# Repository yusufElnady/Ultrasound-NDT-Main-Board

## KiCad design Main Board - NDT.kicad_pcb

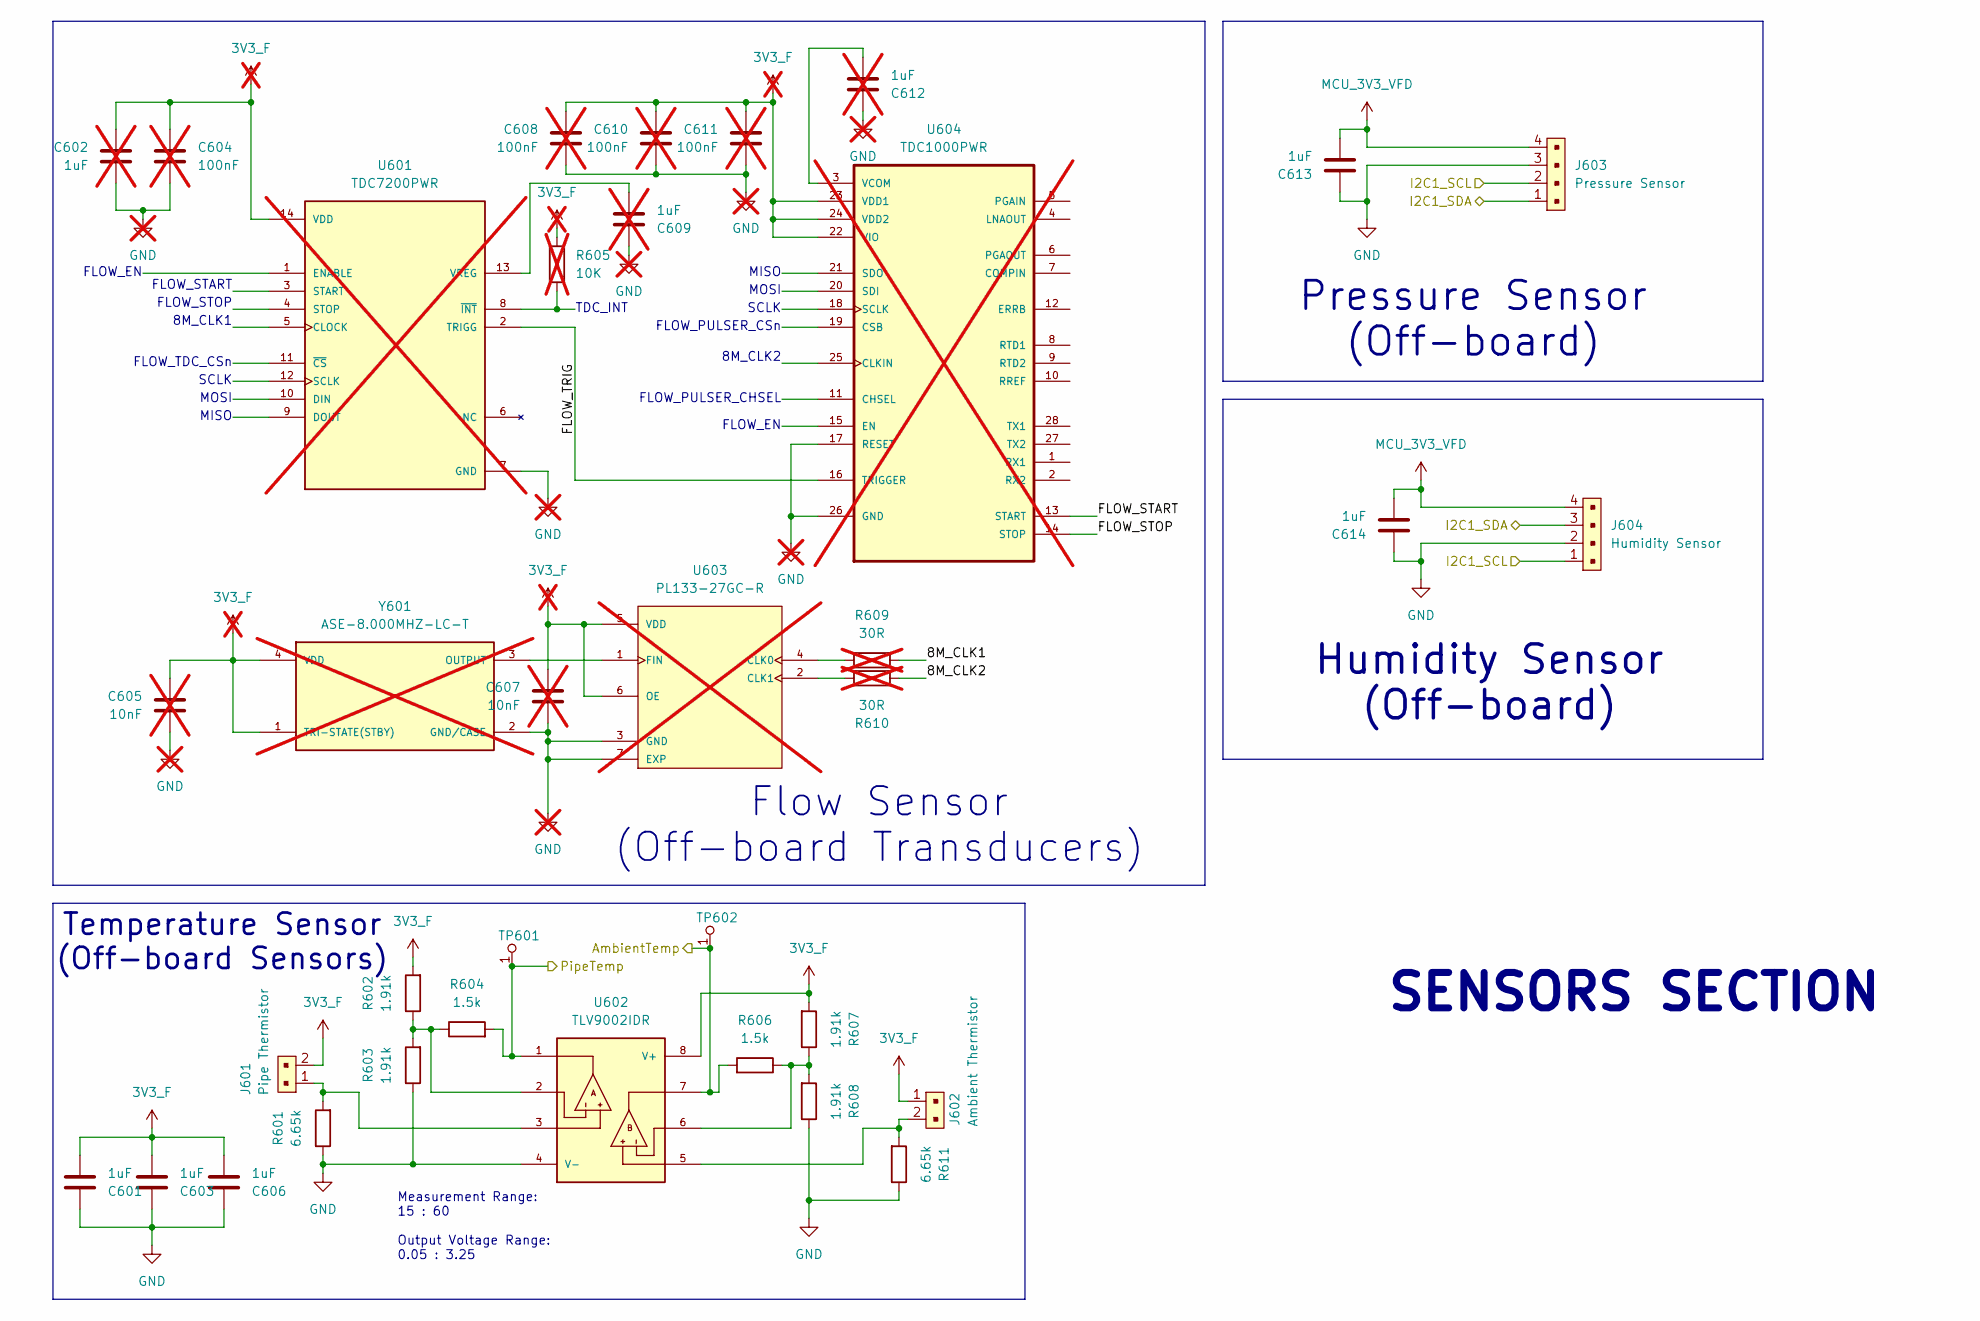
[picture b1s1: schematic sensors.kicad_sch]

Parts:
C601, C603, C606, C613, C614: 1uF; C_0603_1608Metric
C602, C609, C612: 1uF; not fitted
C604, C608, C610, C611: 100nF; C_0603_1608Metric; not fitted
C605, C607: 10nF; C_0603_1608Metric; not fitted
J601: Pipe Thermistor; PinHeader_1x2_P2mm_Drill1mm_RA; MPN S2B-PH-K-S(LF)(SN); Digi-Key_PN 455-1719-ND
J602: Ambient Thermistor; PinHeader_1x2_P2mm_Drill1mm_RA; MPN S2B-PH-K-S(LF)(SN); Digi-Key_PN 455-1719-ND
J603: Pressure Sensor; PinHeader_1x4_P2.5mm_Drill1.1mm; MPN B4B-XH-A(LF)(SN); Digi-Key_PN 455-2249-ND
J604: Humidity Sensor; PinHeader_1x4_P2.5mm_Drill1.1mm; MPN B4B-XH-A(LF)(SN); Digi-Key_PN 455-2249-ND
R601, R611: 6.65k; R_0603_1608Metric
R602, R603, R607, R608: 1.91k; R_0603_1608Metric
R604, R606: 1.5k; R_0603_1608Metric
R605: 10K; not fitted
R609, R610: 30R; not fitted
TP601, TP602: RCT-0C; PROBE_PAD_0805; MPN RCT-0C; Digi-Key_PN A106144CT-ND
U601: TDC7200PWR; SOP65P640X120-14N; PARTREV D; not fitted
U602: TLV9002IDR; SOIC127P599X175-8N; PARTREV O
U603: PL133-27GC-R; SON40P130X200X60-7N; PARTREV 09/13/13; not fitted
U604: TDC1000PWR; SOP65P640X120-28N; not fitted
Y601: ASE-8.000MHZ-LC-T; XTAL_ASE-8.000MHZ-LC-T; PARTREV 02-18-22; not fitted

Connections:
3V3_F: C601.2, C602.1, C603.2, C604.1, C605.1, C606.2, C607.1, C608.1, C610.1, C611.1, J601.2, J602.1, R602.2, R605.1, R607.2, U601.14 (VDD), U602.8 (V+), U603.5 (VDD), U603.6 (OE), U604.22 (VIO), U604.23 (VDD1), U604.24 (VDD2), Y601.1 (TRI-STATE(STBY)), Y601.4 (VDD); also elsewhere on the board
/MCU/AmbientTemp: R606.2, TP602.1, U602.7; also elsewhere on the board
/MCU/I2C1_SCL: J603.2, J604.1; also elsewhere on the board
/MCU/I2C1_SDA: J603.1, J604.3; also elsewhere on the board
/MCU/PipeTemp: R604.2, TP601.1, U602.1; also elsewhere on the board
GND: C601.1, C602.2, C603.1, C604.2, C605.2, C606.1, C607.2, C608.2, C609.1, C610.2, C611.2, C612.1, C613.1, C614.1, J603.3, J604.2, R601.1, R603.1, R608.1, R611.1, U601.7 (GND), U602.4 (V-), U603.3 (GND), U603.7 (EXP), U604.17 (RESET), U604.26 (GND), Y601.2 (GND/CASE); also elsewhere on the board
MCU_3V3_VFD: C613.2, C614.2, J603.4, J604.4; also elsewhere on the board
unnamed: C609.2, U601.13 (VREG)
unnamed: C612.2, U604.3 (VCOM)
unnamed: J601.1, R601.2, U602.3
unnamed: J602.2, R611.2, U602.5
unnamed: R602.1, R603.2, R604.1, U602.2
unnamed: R605.2, U601.8 (~INT)
unnamed: R606.1, R607.1, R608.2, U602.6
unnamed: R609.1, U603.4 (CLK0)
unnamed: R610.2, U603.2 (CLK1)
unnamed: U601.2 (TRIGG), U604.16 (TRIGGER)
unnamed: U603.1 (FIN), Y601.3 (OUTPUT)

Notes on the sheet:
SCLK
MISO
FLOW_STOP
MOSI
FLOW_TDC_CSn
Pressure Sensor (Off-board)
Humidity Sensor (Off-board)
Measurement Range: 15 : 60 Output Voltage Range: 0.05 : 3.25
Flow Sensor (Off-board Transducers)
FLOW_PULSER_CHSEL
FLOW_EN
SENSORS SECTION
FLOW_START
TDC_INT
8M_CLK2
8M_CLK1
Temperature Sensor (Off-board Sensors)
FLOW_PULSER_CSn

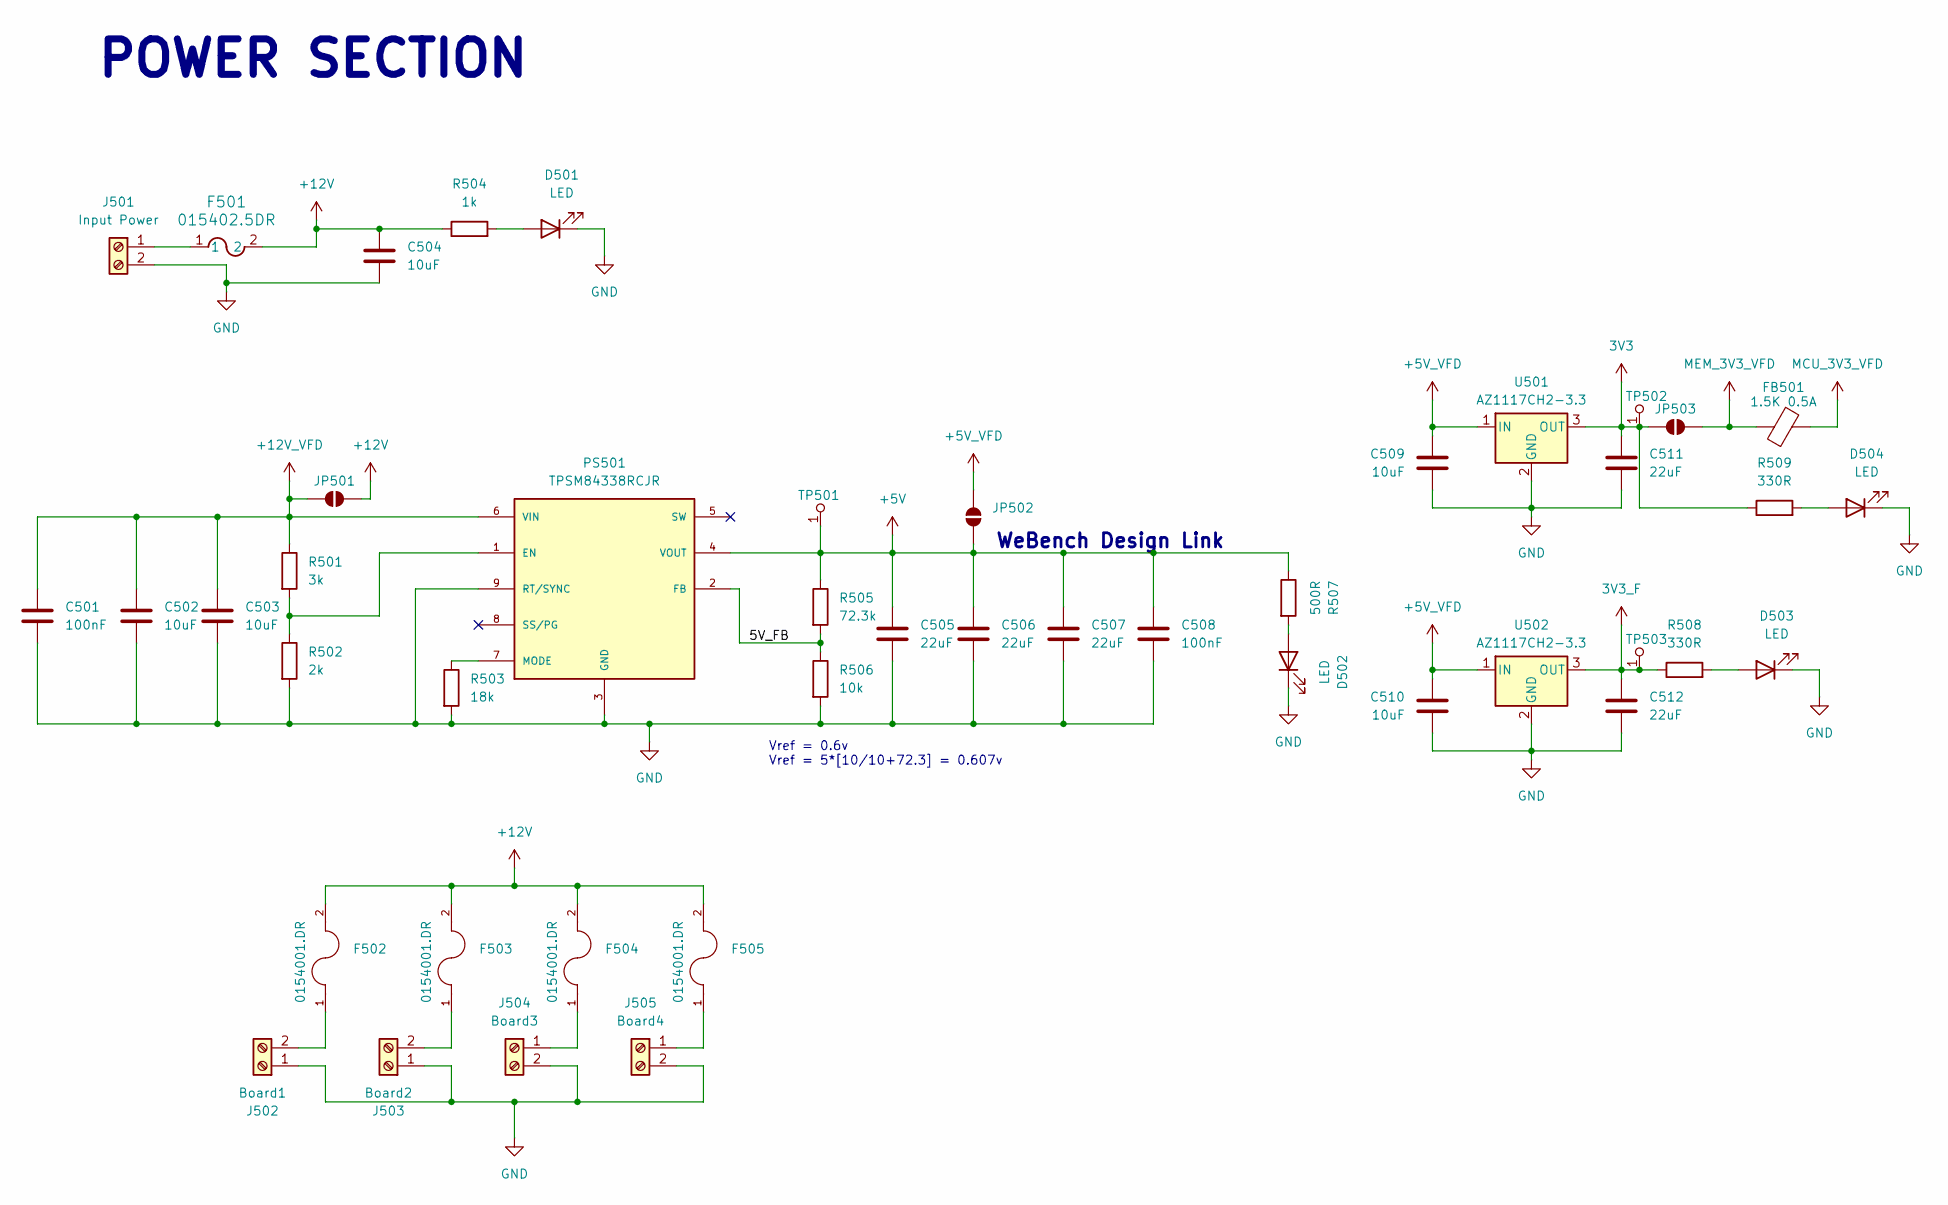
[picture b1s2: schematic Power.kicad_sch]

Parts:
C501, C508: 100nF; C_0603_1608Metric
C502, C503, C504, C509, C510: 10uF; C_0805_2012Metric
C505, C506, C507, C511, C512: 22uF; C_0805_2012Metric
D501, D502, D503, D504: LED; LED_0805_2012Metric
F501: 015402.5DR; 0154Series_LTF
F502, F503, F504, F505: 0154001.DR; FUSE_0154001.DR; PARTREV GD
FB501: 1.5K 0.5A; L_0603_1608Metric
J501: Input Power; TerminalBlock_MaiXu_MX126-5.0-02P_1x02_P5.00mm
J502: Board1; TerminalBlock_MaiXu_MX126-5.0-02P_1x02_P5.00mm
J503: Board2; TerminalBlock_MaiXu_MX126-5.0-02P_1x02_P5.00mm
J504: Board3; TerminalBlock_MaiXu_MX126-5.0-02P_1x02_P5.00mm
J505: Board4; TerminalBlock_MaiXu_MX126-5.0-02P_1x02_P5.00mm
JP501: SolderJumper_2_Open; SolderJumper-2_P1.3mm_Open_RoundedPad1.0x1.5mm
JP502, JP503: SolderJumper_2_Open; SolderJumper-2_P1.3mm_Open_Pad1.0x1.5mm
PS501: TPSM84338RCJR; CONV_TPSM84338RCJR; PARTREV November 2024
R501: 3k; R_0603_1608Metric
R502: 2k; R_0603_1608Metric
R503: 18k; R_0603_1608Metric
R504: 1k; R_0603_1608Metric
R505: 72.3k; R_0603_1608Metric
R506: 10k; R_0603_1608Metric
R507: 500R; R_0603_1608Metric
R508, R509: 330R; R_0603_1608Metric
TP501, TP502, TP503: RCT-0C; PROBE_PAD_0805; MPN RCT-0C; Digi-Key_PN A106144CT-ND
U501, U502: AZ1117CH2-3.3; SOT-223-3_TabPin2

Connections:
3V3: C511.1, JP503.1 (A), R509.1, TP502.1, U501.3 (OUT)
3V3_F: C512.1, R508.1, TP503.1, U502.3 (OUT); also elsewhere on the board
+5V: C505.1, C506.1, C507.1, C508.1, JP502.1 (A), PS501.4 (VOUT), R505.1, R507.1, TP501.1
+5V_VFD: C509.1, C510.1, JP502.2 (B), U501.1 (IN), U502.1 (IN); also elsewhere on the board
+12V: C504.1, F501.2, F502.2, F503.2, F504.2, F505.2, JP501.2 (B), R504.1
+12V_VFD: C501.1, C502.1, C503.1, JP501.1 (A), PS501.6 (VIN), R501.1
/Power/5V_FB: PS501.2 (FB), R505.2, R506.1
GND: C501.2, C502.2, C503.2, C504.2, C505.2, C506.2, C507.2, C508.2, C509.2, C510.2, C511.2, C512.2, D501.1 (K), D502.1 (K), D503.1 (K), D504.1 (K), J501.2, J502.1, J503.1, J504.2, J505.2, PS501.3 (GND), PS501.9 (RT/SYNC), R502.2, R503.2, R506.2, U501.2 (GND), U502.2 (GND); also elsewhere on the board
MCU_3V3_VFD: FB501.2; also elsewhere on the board
MEM_3V3_VFD: FB501.1, JP503.2 (B); also elsewhere on the board
unnamed: D501.2 (A), R504.2
unnamed: D502.2 (A), R507.2
unnamed: D503.2 (A), R508.2
unnamed: D504.2 (A), R509.2
unnamed: F501.1, J501.1
unnamed: F502.1, J502.2
unnamed: F503.1, J503.2
unnamed: F504.1, J504.1
unnamed: F505.1, J505.1
unnamed: PS501.1 (EN), R501.2, R502.1
unnamed: PS501.7 (MODE), R503.1

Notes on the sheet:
WeBench Design Link
Vref = 0.6v Vref = 5*[10/10+72.3] = 0.607v
POWER SECTION

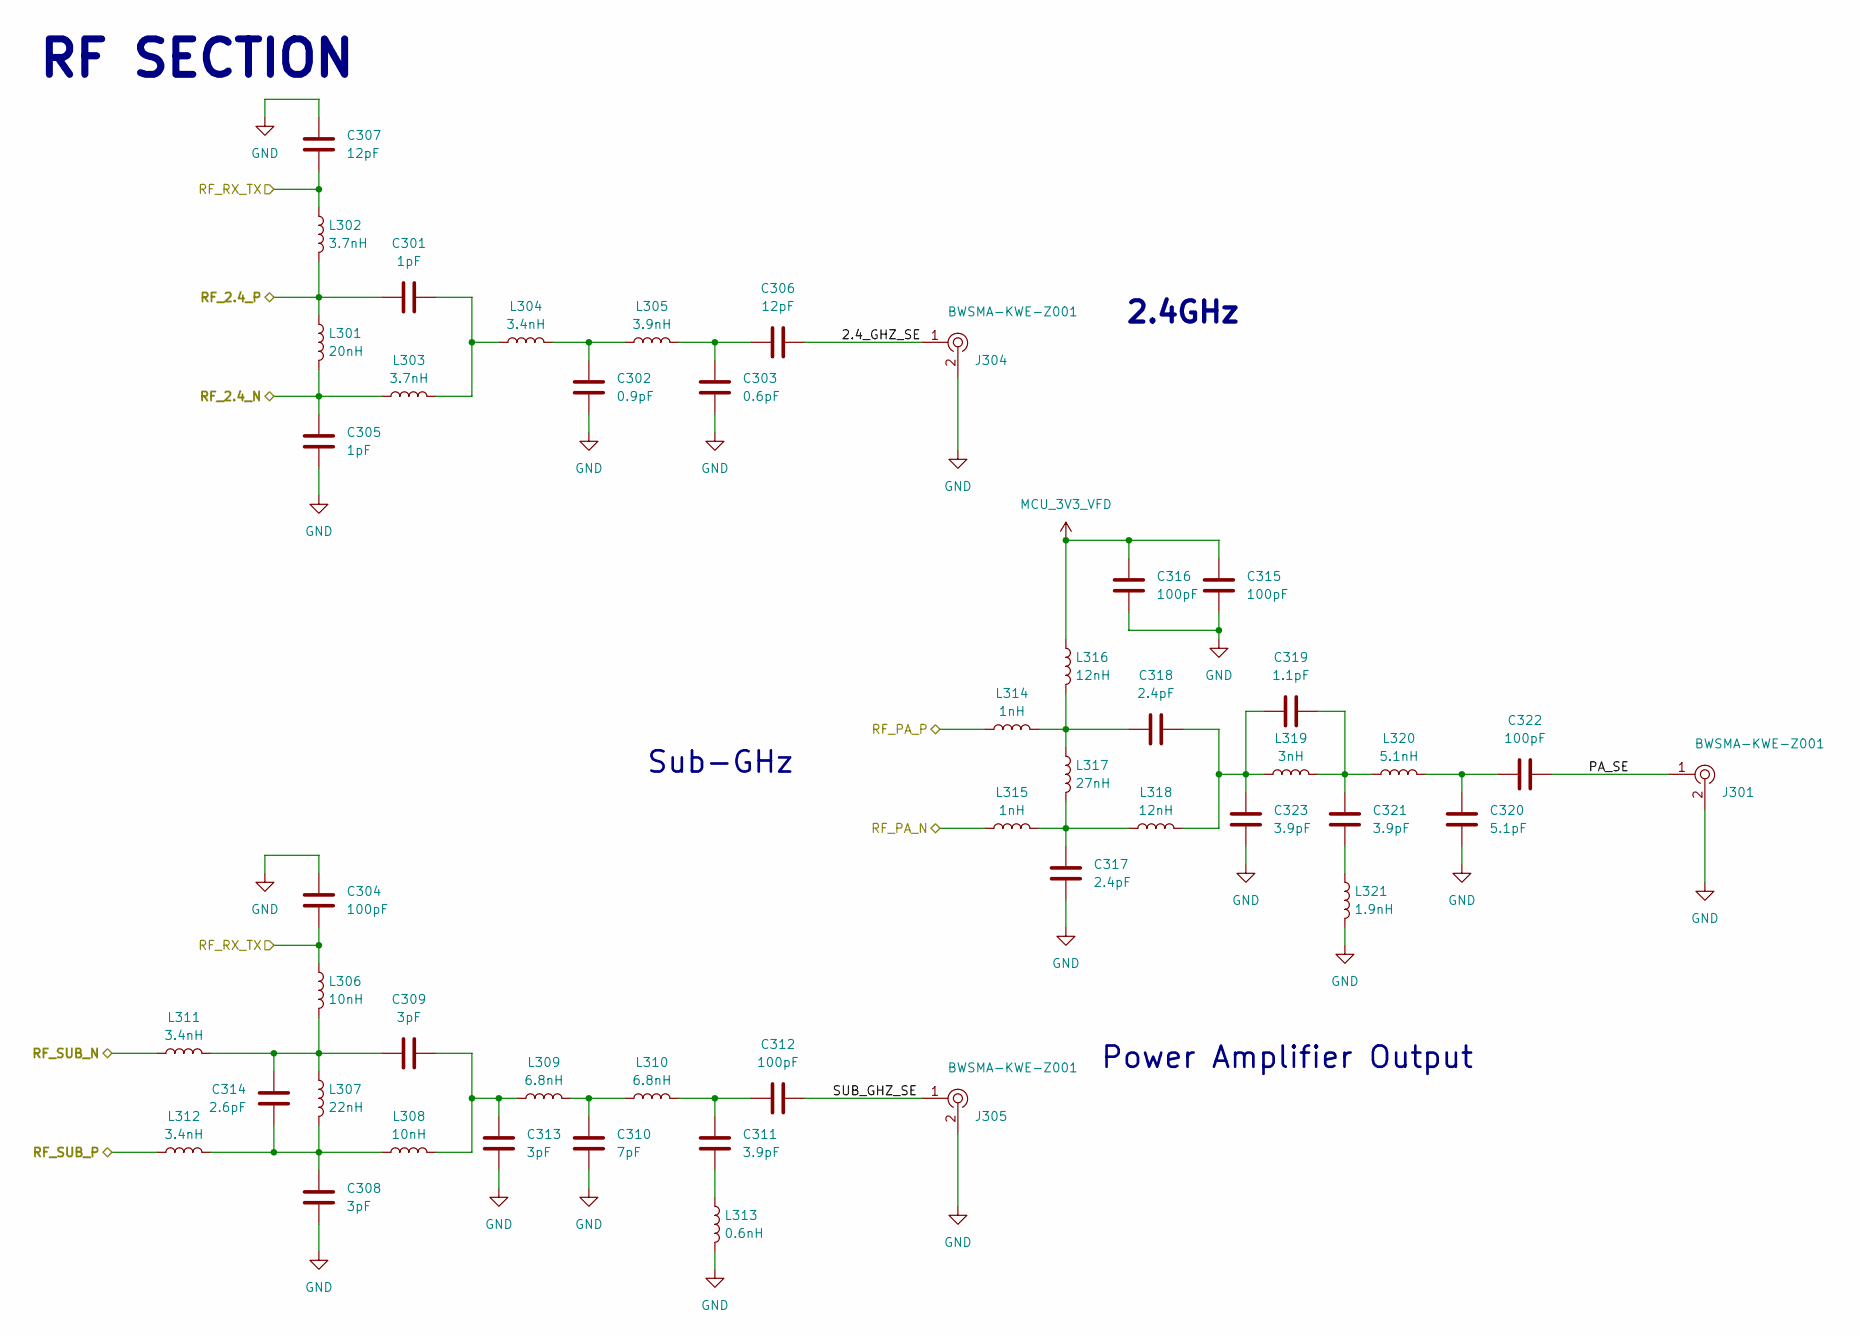
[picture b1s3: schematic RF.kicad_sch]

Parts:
C301, C305: 1pF; C_0402_1005Metric
C302: 0.9pF; C_0402_1005Metric
C303: 0.6pF; C_0402_1005Metric
C304, C312, C315, C316, C322: 100pF; C_0402_1005Metric
C306, C307: 12pF; C_0402_1005Metric
C308, C309, C313: 3pF; C_0402_1005Metric
C310: 7pF; C_0402_1005Metric
C311, C321, C323: 3.9pF; C_0402_1005Metric
C314: 2.6pF; C_0402_1005Metric
C317, C318: 2.4pF; C_0402_1005Metric
C319: 1.1pF; C_0402_1005Metric
C320: 5.1pF; C_0402_1005Metric
J301, J304, J305: BWSMA-KWE-Z001; RF_SMA_RightAngle_5-1814400-1; MPN BWSMA-KWE-Z001; LCSC PN C496551
L301: 20nH; L_0402_1005Metric
L302, L303: 3.7nH; L_0402_1005Metric
L304, L311, L312: 3.4nH; L_0402_1005Metric
L305: 3.9nH; L_0402_1005Metric
L306, L308: 10nH; L_0402_1005Metric
L307: 22nH; L_0402_1005Metric
L309, L310: 6.8nH; L_0402_1005Metric
L313: 0.6nH; L_0402_1005Metric
L314, L315: 1nH; L_0402_1005Metric
L316, L318: 12nH; L_0402_1005Metric
L317: 27nH; L_0402_1005Metric
L319: 3nH; L_0402_1005Metric
L320: 5.1nH; L_0402_1005Metric
L321: 1.9nH; L_0402_1005Metric

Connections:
/MCU/RF_2.4_N: C301.1, L301.1, L302.2; also elsewhere on the board
/MCU/RF_2.4_P: C305.2, L301.2, L303.1; also elsewhere on the board
/MCU/RF_PA_N: L315.1; also elsewhere on the board
/MCU/RF_PA_P: L314.1; also elsewhere on the board
/MCU/RF_RX_TX: C304.1, C307.1, L302.1, L306.1; also elsewhere on the board
/MCU/RF_SUB_N: L311.1; also elsewhere on the board
/MCU/RF_SUB_P: L312.1; also elsewhere on the board
/RF/2.4_GHZ_SE: C306.2, J304.1
/RF/PA_SE: C322.1, J301.1
/RF/SUB_GHZ_SE: C312.1, J305.1
GND: C302.1, C303.1, C304.2, C305.1, C307.2, C308.1, C310.1, C313.1, C315.1, C316.1, C317.1, C320.1, C323.1, J301.2, J304.2, J305.2, L313.2, L321.2; also elsewhere on the board
MCU_3V3_VFD: C315.2, C316.2, L316.1; also elsewhere on the board
unnamed: C301.2, L303.2, L304.1
unnamed: C302.2, L304.2, L305.1
unnamed: C303.2, C306.1, L305.2
unnamed: C308.2, C314.2, L307.2, L308.1, L312.2
unnamed: C309.1, C314.1, L306.2, L307.1, L311.2
unnamed: C309.2, C313.2, L308.2, L309.1
unnamed: C310.2, L309.2, L310.1
unnamed: C311.1, L313.1
unnamed: C311.2, C312.2, L310.2
unnamed: C317.2, L315.2, L317.2, L318.1
unnamed: C318.1, L314.2, L316.2, L317.1
unnamed: C318.2, C319.1, C323.2, L318.2, L319.1
unnamed: C319.2, C321.2, L319.2, L320.1
unnamed: C320.2, C322.2, L320.2
unnamed: C321.1, L321.1

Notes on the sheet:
RF SECTION
Power Amplifier Output
Sub-GHz
2.4GHz

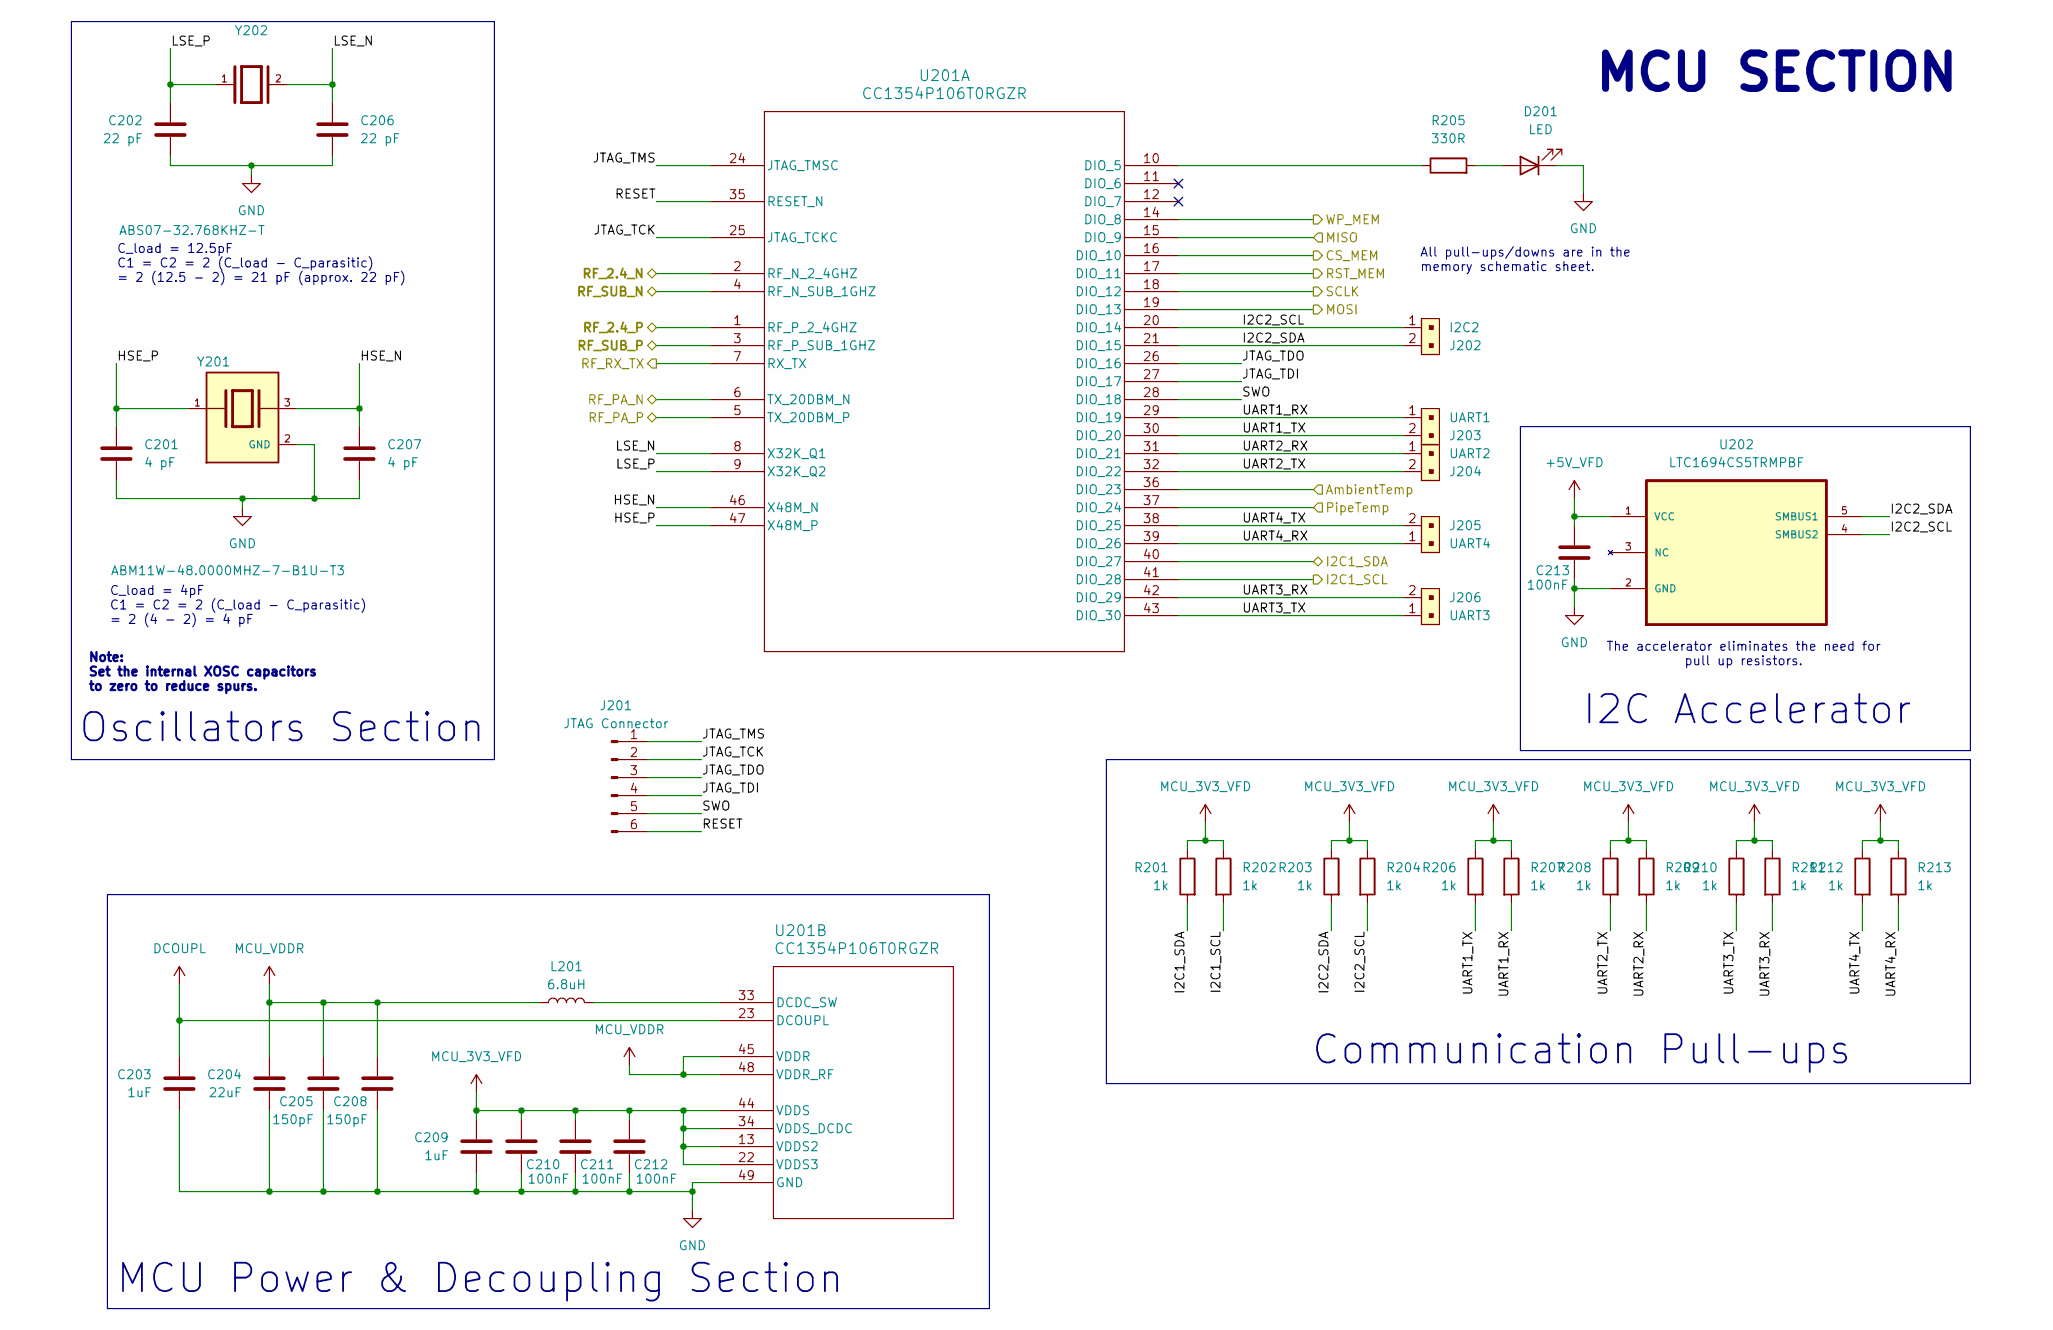
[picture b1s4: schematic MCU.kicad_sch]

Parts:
C201, C207: 4 pF; C_0603_1608Metric
C202, C206: 22 pF; C_0603_1608Metric
C203, C209: 1uF; C_0603_1608Metric
C204: 22uF; C_0805_2012Metric
C205, C208: 150pF; C_0603_1608Metric
C210, C211, C212, C213: 100nF; C_0603_1608Metric
D201: LED; LED_0805_2012Metric
J201: JTAG Connector; PinHeader_1x06_P2.54mm_Vertical
J202: I2C2; PinHeader_1x2_P2mm_Drill1mm_RA; MPN S2B-PH-K-S(LF)(SN); Digi-Key_PN 455-1719-ND
J203: UART1; PinHeader_1x2_P2mm_Drill1mm_RA; MPN S2B-PH-K-S(LF)(SN); Digi-Key_PN 455-1719-ND
J204: UART2; PinHeader_1x2_P2mm_Drill1mm_RA; MPN S2B-PH-K-S(LF)(SN); Digi-Key_PN 455-1719-ND
J205: UART4; PinHeader_1x2_P2mm_Drill1mm_RA; MPN S2B-PH-K-S(LF)(SN); Digi-Key_PN 455-1719-ND
J206: UART3; PinHeader_1x2_P2mm_Drill1mm_RA; MPN S2B-PH-K-S(LF)(SN); Digi-Key_PN 455-1719-ND
L201: 6.8uH; L_0805_2012Metric
R201, R202, R203, R204, R206, R207, R208, R209, R210, R211, R212, R213: 1k; R_0603_1608Metric
R205: 330R; R_0603_1608Metric
U201: CC1354P106T0RGZR; VQFN48_RGZ_TEX
U202: LTC1694CS5TRMPBF; SOT95P280X100-5N; MPN LTC1694CS5#TRMPBF
Y201: ABM11W-48.0000MHZ-7-B1U-T3; XTAL_ABM11W-48.0000MHZ-7-B1U-T3; PARTREV 10.06.2020
Y202: ABS07-32.768KHZ-T; XTAL_ABS07-32.768KHZ-T; PARTREV 08.19.15

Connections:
+5V_VFD: C213.1, U202.1 (VCC); also elsewhere on the board
/MCU/AmbientTemp: U201.36 (DIO_23); also elsewhere on the board
/MCU/CS_MEM: U201.16 (DIO_10); also elsewhere on the board
/MCU/HSE_N: C207.1, U201.46 (X48M_N), Y201.3
/MCU/HSE_P: C201.1, U201.47 (X48M_P), Y201.1
/MCU/I2C1_SCL: R202.2, U201.41 (DIO_28); also elsewhere on the board
/MCU/I2C1_SDA: R201.2, U201.40 (DIO_27); also elsewhere on the board
/MCU/I2C2_SCL: J202.1, R204.2, U201.20 (DIO_14), U202.4 (SMBUS2)
/MCU/I2C2_SDA: J202.2, R203.2, U201.21 (DIO_15), U202.5 (SMBUS1)
/MCU/JTAG_TCK: J201.2, U201.25 (JTAG_TCKC)
/MCU/JTAG_TDI: J201.4, U201.27 (DIO_17)
/MCU/JTAG_TDO: J201.3, U201.26 (DIO_16)
/MCU/JTAG_TMS: J201.1, U201.24 (JTAG_TMSC)
/MCU/LSE_N: C206.1, U201.8 (X32K_Q1), Y202.2
/MCU/LSE_P: C202.1, U201.9 (X32K_Q2), Y202.1
/MCU/MISO: U201.15 (DIO_9); also elsewhere on the board
/MCU/MOSI: U201.19 (DIO_13); also elsewhere on the board
/MCU/PipeTemp: U201.37 (DIO_24); also elsewhere on the board
/MCU/RESET: J201.6, U201.35 (RESET_N)
/MCU/RF_2.4_N: U201.2 (RF_N_2_4GHZ); also elsewhere on the board
/MCU/RF_2.4_P: U201.1 (RF_P_2_4GHZ); also elsewhere on the board
/MCU/RF_PA_N: U201.6 (TX_20DBM_N); also elsewhere on the board
/MCU/RF_PA_P: U201.5 (TX_20DBM_P); also elsewhere on the board
/MCU/RF_RX_TX: U201.7 (RX_TX); also elsewhere on the board
/MCU/RF_SUB_N: U201.4 (RF_N_SUB_1GHZ); also elsewhere on the board
/MCU/RF_SUB_P: U201.3 (RF_P_SUB_1GHZ); also elsewhere on the board
/MCU/RST_MEM: U201.17 (DIO_11); also elsewhere on the board
/MCU/SCLK: U201.18 (DIO_12); also elsewhere on the board
/MCU/SWO: J201.5, U201.28 (DIO_18)
/MCU/UART1_RX: J203.1, R207.2, U201.29 (DIO_19)
/MCU/UART1_TX: J203.2, R206.2, U201.30 (DIO_20)
/MCU/UART2_RX: J204.1, R209.2, U201.31 (DIO_21)
/MCU/UART2_TX: J204.2, R208.2, U201.32 (DIO_22)
/MCU/UART3_RX: J206.2, R211.2, U201.42 (DIO_29)
/MCU/UART3_TX: J206.1, R210.2, U201.43 (DIO_30)
/MCU/UART4_RX: J205.1, R213.2, U201.39 (DIO_26)
/MCU/UART4_TX: J205.2, R212.2, U201.38 (DIO_25)
/MCU/WP_MEM: U201.14 (DIO_8); also elsewhere on the board
DCOUPL: C203.1, U201.23 (DCOUPL)
GND: C201.2, C202.2, C203.2, C204.2, C205.1, C206.2, C207.2, C208.1, C209.2, C210.2, C211.2, C212.2, C213.2, D201.1 (K), U201.49 (GND), U202.2 (GND), Y201.2 (GND), Y201.4 (GND); also elsewhere on the board
MCU_3V3_VFD: C209.1, C210.1, C211.1, C212.1, R201.1, R202.1, R203.1, R204.1, R206.1, R207.1, R208.1, R209.1, R210.1, R211.1, R212.1, R213.1, U201.13 (VDDS2), U201.22 (VDDS3), U201.34 (VDDS_DCDC), U201.44 (VDDS); also elsewhere on the board
MCU_VDDR: C204.1, C205.2, C208.2, L201.1, U201.45 (VDDR), U201.48 (VDDR_RF)
unnamed: D201.2 (A), R205.2
unnamed: R205.1, U201.10 (DIO_5)
unnamed: L201.2, U201.33 (DCDC_SW)

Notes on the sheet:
All pull-ups/downs are in the memory schematic sheet.
Communication Pull-ups
C_load = 12.5pF C1 = C2 = 2 (C_load - C_parasitic) = 2 (12.5 - 2) = 21 pF (approx. 22 pF)
MCU Power & Decoupling Section
Oscillators Section
I2C Accelerator
C_load = 4pF C1 = C2 = 2 (C_load - C_parasitic) = 2 (4 - 2) = 4 pF
Note: Set the internal XOSC capacitors to zero to reduce spurs.
MCU SECTION
The accelerator eliminates the need for pull up resistors.

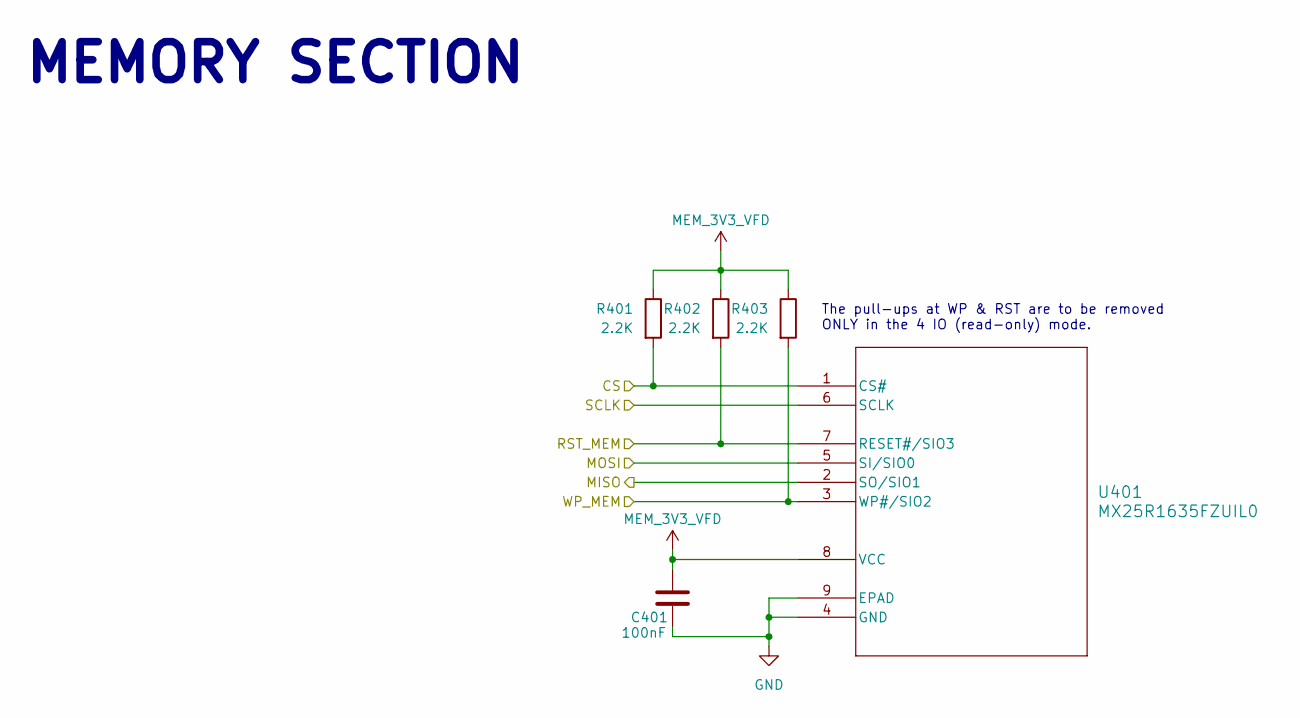
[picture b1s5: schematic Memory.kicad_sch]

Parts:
C401: 100nF; C_0603_1608Metric
R401, R402, R403: 2.2K; R_0603_1608Metric
U401: MX25R1635FZUIL0; USON-8L-2X3X0P6_MAC

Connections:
/MCU/CS_MEM: R401.2, U401.1 (CS#); also elsewhere on the board
/MCU/MISO: U401.2 (SO/SIO1); also elsewhere on the board
/MCU/MOSI: U401.5 (SI/SIO0); also elsewhere on the board
/MCU/RST_MEM: R402.2, U401.7 (RESET#/SIO3); also elsewhere on the board
/MCU/SCLK: U401.6 (SCLK); also elsewhere on the board
/MCU/WP_MEM: R403.2, U401.3 (WP#/SIO2); also elsewhere on the board
GND: C401.2, U401.4 (GND), U401.9 (EPAD); also elsewhere on the board
MEM_3V3_VFD: C401.1, R401.1, R402.1, R403.1, U401.8 (VCC); also elsewhere on the board

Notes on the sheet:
MEMORY SECTION
The pull-ups at WP & RST are to be removed ONLY in the 4 IO (read-only) mode.
